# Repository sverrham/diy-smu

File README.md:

# diy-smu
DIY Source Measurement Unit, four quadrant powersupply and ?.? digit volt/current meter.

This is based on http://www.djerickson.com/diy_smu/index.html but with some changes.

- I plan to use the raspberry pi for control, maybe design a front pannel solution using the compute module.

- I want to miniturize it a bit, change 0805 to 0603 as that is also quite easy to solder by hand.

- I do not have to much experience with the analog part but will let this be project to learn from.

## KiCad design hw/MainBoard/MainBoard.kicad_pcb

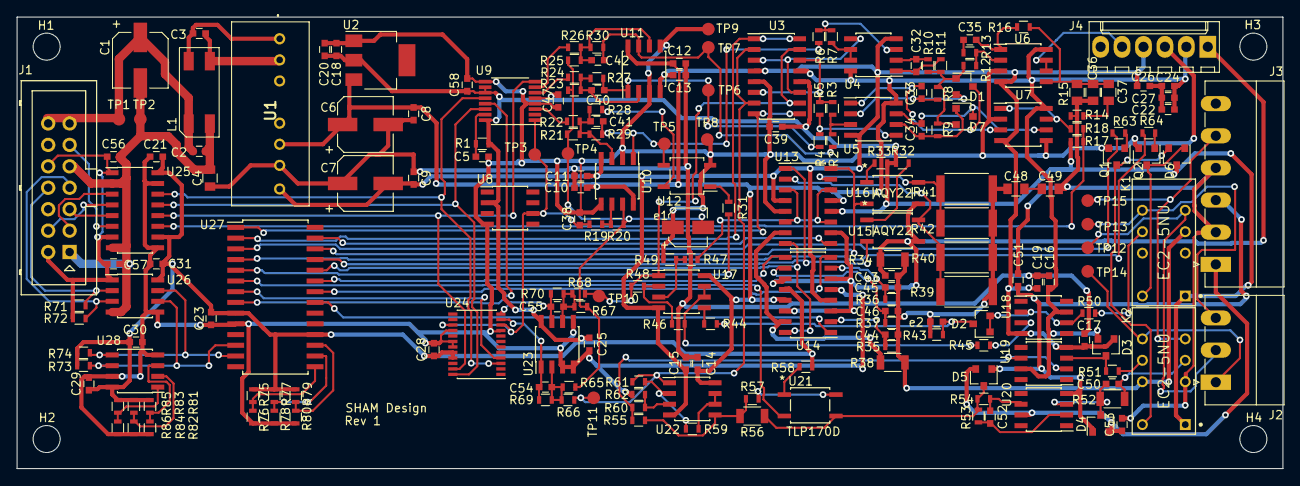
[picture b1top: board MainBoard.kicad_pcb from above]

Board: 2 copper layers, 150.0 x 53.5 mm, 209 parts (0 on the bottom side), 130 nets.

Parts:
C1, C6, C7: 47uf 25V; CP_Elec_6.3x7.7
C2, C3, C8, C9, C18, C20, C57: 4.7u 25V; C_0603
C4: .01u 500V; C_0805
C5, C10, C11, C12, C13, C14, C15, C16, C17, C19, C21, C22, C23, C24, C25, C26, C27, C28, C29, C30, C31, C38, C39, C47, C51, C53, C56, C58: .1u; C_0603
C32, C33, C34: 15p; C_0603
C35, C40, C41, C42, C54, C55: 1000p; C_0603
C36: 22p 500V DNI; C_0805
C37: 150p 500V; C_0805
C43: 100p; C_0603
C44, C45, C46: 270p; C_0603
C48, C49: 270p HIV COG 500V; C_0805
C50: 22p 100V; C_0603
C52: 150p; C_0603
D1: BAV99LT1; SOT-23
D2, D3, D4, D5: BAV199; SOT-23
D6: BAV170; SOT-23
D7: BAV199LT1; SOT-23
H1, H2, H3, H4: MountingHole; MountingHole_3.2mm_M3
J1: Conn_01x14; Multicomp_MC9A12-1434_2x07x2.54mm_Straight
J2: Conn_01x03_Female; PhoenixContact_MC-G_03x3.81mm_Angled
J3: Conn_01x06_Female; PhoenixContact_MC-G_06x3.81mm_Angled
J4: Conn_01x06_Female; Molex_KK-6410-06_06x2.54mm_Straight
K1, K2: EC2-5NU; Kemet-EC2-5NU-0
L1: DR331-105BE; dr331
Q1, Q2: MMBT3904; SOT-23
R1: 100K; R_0603
R2, R3, R4, R5, R6, R7, R19, R20, R21, R22, R23, R24, R25, R26, R55, R59, R60, R61, R62, R65, R67, R69, R70: 10K .1%; R_0603
R8, R9: 20K; R_0603
R10: 20K .1%; R_0603
R11, R17, R51, R54: 4.99K; R_0603
R12, R13, R16, R43, R44, R53, R63, R64: 10K; R_0603
R14, R45: 1K; R_0603
R15: 200K 1206; C_0805
R18: 15K; R_0603
R27, R30, R66, R68: 21.5K .1%; R_0603
R28: 2K .1%; R_0603
R29: 20.5K .1%; R_0603
R31, R32, R33, R50, R58: 2K; R_0603
R34: 5M 25ppm 1206; R_1206
R35: 560K .1%; R_0603
R36: 49.9K .1%; R_0603
R37: 4.99K .1%; R_0603
R38: 499 .25W; R_1206
R39, R40: 100 1W; R_2512
R41, R42: 2 1W; R_2512
R46, R47, R48, R49: 100K .1%; R_0603
R52: 10K 1206; R_1206
R56: 300K .1% 1206; R_1206
R57: 22.1K .1%; R_0603
R71, R72, R73, R74: 1.5K; R_0603
R75, R76, R77, R78, R79, R80, R81, R82, R83, R84, R85, R86: 0; R_0603
TP1: TP+12; Measurement_Point_Round-SMD-Pad_Small
TP2: TPIGND; Measurement_Point_Round-SMD-Pad_Small
TP3: TPR+; Measurement_Point_Round-SMD-Pad_Small
TP4: TPR-; Measurement_Point_Round-SMD-Pad_Small
TP5: TPF; Measurement_Point_Round-SMD-Pad_Small
TP6: TPC-; Measurement_Point_Round-SMD-Pad_Small
TP7: TPC+; Measurement_Point_Round-SMD-Pad_Small
TP8: TPG; Measurement_Point_Round-SMD-Pad_Small
TP9: TPG1; Measurement_Point_Round-SMD-Pad_Small
TP10: TPIM; Measurement_Point_Round-SMD-Pad_Small
TP11: TPVM; Measurement_Point_Round-SMD-Pad_Small
TP12: TP+Out; Measurement_Point_Round-SMD-Pad_Small
TP13: TP+Gua; Measurement_Point_Round-SMD-Pad_Small
TP14: TP+Sen; Measurement_Point_Round-SMD-Pad_Small
TP15: TP-Sen; Measurement_Point_Round-SMD-Pad_Small
U1: DPBW03F; DPBW03F15
U2: LT1117-5.0; SOT-223
U3, U13, U14: DG444; SOIC-16_3.9x9.9mm_Pitch1.27mm
U4, U5, U6, U10, U17, U22: OPA2140; SOIC-8_3.9x4.9mm_Pitch1.27mm
U7: LM393; SOIC-8_3.9x4.9mm_Pitch1.27mm
U8: ADR431ARZ; SOIC-8_3.9x4.9mm_Pitch1.27mm
U9: AD5686RBRUZ; TSSOP-16_4.4x5mm_Pitch0.65mm
U11: TL072; SOIC-8_3.9x4.9mm_Pitch1.27mm
U12: CPC1018N; SOP-4_3.8x4.1mm_Pitch2.54mm
U15, U16: AQY22; TLP170DF
U18: TL071; SOIC-8_3.9x4.9mm_Pitch1.27mm
U19, U20: OPA140; SOIC-8_3.9x4.9mm_Pitch1.27mm
U21: TLP170D; TLP170DF
U23: TLC227x; SOIC-8_3.9x4.9mm_Pitch1.27mm
U24: AD7190BRUZ; TSSOP-24_4.4x7.8mm_Pitch0.65mm
U25: Si8642BB-B-IS1; SOIC-16_3.9x9.9mm_Pitch1.27mm
U26: ISO1541; SOIC-8_3.9x4.9mm_Pitch1.27mm
U27: MCP23017_SO; SOIC-28W_7.5x17.9mm_Pitch1.27mm
U28: 24LC01; SOIC-8_3.9x4.9mm_Pitch1.27mm
e1: 4.7uf 25V; CP_Elec_4x5.3
e2: 22p 100V; C_0603

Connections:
/1A: U13.16, U16.2, U27.26
/1mA: U14.9, U27.23
/10mA: U13.8, U14.16, U27.24
/10uA: U14.1, U27.21
/100mA: U13.1, U15.2, U27.25
/100uA: U14.8, U27.22
/+2.5VREF: C38.1, R19.2, TP3.1, U8.6, U9.1, U24.10, U24.15
/+5V: C18.1, C20.1, C21.1, C23.1, C25.1, C28.1, C29.1, C30.1, C31.1, C39.1, C47.1, C58.1, D6.3, K1.1, K2.1, R1.2, R17.2, R32.1, R33.1, R58.1, R73.1, R74.1, R75.1, R77.1, R79.1, R81.1, R83.1, R85.1, U2.2, U3.12, U8.2, U9.5, U9.10, U9.11, U9.16, U13.12, U14.12, U23.8, U24.20, U24.21, U25.10, U25.16, U26.8, U27.9, U27.18, U28.8
/+5VIN: C56.1, C57.1, J1.2, J1.10, R71.1, R72.1, U25.1, U25.7, U26.1
/+12VIN: C1.1, C2.1, J1.13, J1.14, L1.1, TP1.1
/+15V: C6.1, C8.1, C10.1, C12.1, C14.1, C16.1, C22.1, C24.1, C27.1, D3.2, J4.2, U1.6, U2.3, U3.13, U4.8, U5.8, U6.8, U7.8, U10.8, U11.8, U13.13, U14.13, U17.8, U18.7, U19.7, U22.8
/-2.5VREF: R20.1, R21.2, R23.2, R25.2, R65.2, R67.2, TP4.1, U10.7, e1.2
/-15V: C7.2, C9.2, C11.2, C13.2, C15.2, C17.2, C19.2, C26.2, D3.1, J4.4, U1.8, U3.4, U4.4, U5.4, U6.4, U7.4, U10.4, U11.4, U13.4, U14.4, U17.4, U18.4, U19.4, U22.4
/ADC/IM: R48.1, R68.2, TP10.1, U3.10, U3.15, U17.1
/ADC/IMADC: C55.2, R70.1, U23.7, U24.12
/ADC/VM: R61.1, R66.2, TP11.1, U3.2, U3.7, U22.1
/ADC/VMADC: C54.2, R69.1, U23.1, U24.11
/CLAMP: J1.11, U25.6
/CS_ADC: U24.4, U27.7
/CS_DAC: U9.13, U27.8
/FDACLO: R31.1, U27.5
/ICLAMP: R17.1, R18.2, U25.11
/IIC_SCL: J1.7, R72.2, U26.3
/IIC_SDA: J1.8, R71.2, U26.2
/IMISO: U9.8, U24.23, U25.12
/IMODE: U3.8, U3.9, U27.1
/IMOSI: U9.14, U24.24, U25.13
/ISCK: U9.12, U24.3, U25.14
/Isolation and Controll/ISCL: R73.2, U26.6, U27.12, U28.6
/Isolation and Controll/ISDA: R74.2, U26.7, U27.13, U28.5
/LT10mA: U13.9, U27.27
/MISO: J1.5, U25.5
/MOSI: J1.4, U25.4
/OCOM: C36.1, C49.2, C51.2, C53.2, J3.2, J3.4, K2.3, R14.2, R15.2
/ON: R64.2, U27.4
/REMOTE: R63.2, U27.3
/SCK: J1.3, U25.3
/VMODE: U3.1, U3.16, U27.2
/VRANGEL: U21.2, U27.6
/crossover/AMPIN: J4.5, U6.6, U6.7
/crossover/CL+: C42.1, R2.2, R30.1, TP7.1, U11.7
/crossover/CL-: C40.2, R4.2, R27.1, TP6.1, U11.1
/crossover/CLM: R3.2, R5.2, U3.6, U3.14
/crossover/FDACN: C41.1, R6.2, R29.1, TP5.1, U10.1, U12.3
/crossover/FM: R7.2, U4.6, U4.7
/crossover/INT: C35.2, R16.2, U6.1
/current measure/+Guard: K1.9, R50.1
/current measure/+OUT_INT: C43.1, C44.1, C45.1, C46.1, C48.1, K1.4, K2.10, R34.1, R35.1, R36.1, R37.1, R38.1, R39.1, R40.1, R41.1, R42.1, R43.2, e2.2
/current measure/AMPGND: C43.2, J4.1, R34.2, U13.10, U14.3, U14.6, U14.11, U14.14, U15.3, U16.3
/current measure/INT_GUARD: D2.1, D2.2, R50.2, U18.2, U18.6
/dac/DAC_CL+: R26.2, U9.7
/dac/DAC_CL-: R24.2, U9.6
/dac/DAC_F: R22.2, U9.3
/frontend/+15VOUT: C53.1, D4.2, D5.2, J3.1, U20.7
/frontend/+GOUT: J2.3, K1.8, TP13.1
/frontend/+OUT: J2.2, K1.5, TP12.1
/frontend/+SEN: J2.1, K2.8, TP14.1
/frontend/+SEN_INT: K2.9, R51.2
/frontend/-15VOUT: C51.1, D4.1, D5.1, J3.3, U20.4
/frontend/-SEN: J3.5, K2.5, TP15.1
/frontend/-SEN_INT: C50.2, K2.4, R52.2
/frontend/ON_RLY: D6.1, K1.12, Q2.3
/frontend/REM_RLY: D6.2, K2.12, Q1.3
/reset: C5.1, R1.1, U9.15
GND1: C5.2, C18.2, C20.2, C21.2, C23.2, C25.2, C28.2, C29.2, C30.2, C31.2, C38.2, C39.2, C47.2, C58.2, J4.3, Q1.2, Q2.2, R49.1, R62.1, R76.2, R78.2, R80.2, R82.2, R84.2, R86.2, TP8.1, TP9.1, U2.1, U3.5, U6.3, U7.2, U7.5, U8.4, U9.4, U9.9, U10.2, U10.5, U11.3, U11.5, U12.2, U13.5, U14.5, U23.3, U23.4, U23.5, U24.9, U24.16, U24.18, U24.19, U25.9, U25.15, U26.5, U27.10, U28.4, U28.7, e1.1
GNDREF: C1.2, C2.2, C4.2, C56.2, C57.2, J1.1, J1.9, L1.2, TP2.1, U25.2, U25.8, U26.4
unnamed: C3.1, L1.4, U1.1
unnamed: C3.2, L1.3, U1.2
unnamed: C4.1, C6.2, C7.1, C8.2, C9.1, C10.2, C11.1, C12.2, C13.1, C14.2, C15.1, C16.2, C17.1, C19.1, U1.7
unnamed: C22.2, C24.2, C26.1, C27.2
unnamed: C32.1, R10.2, U4.2
unnamed: C32.2, R11.2, U4.1
unnamed: C33.1, D1.3, U5.1, U7.3
unnamed: C33.2, D1.2, R8.2, U5.2
unnamed: C34.1, D7.3, U5.7, U7.6
unnamed: C34.2, D7.1, R9.2, U5.6
unnamed: C35.1, R13.1
unnamed: C36.2, C37.2, R15.1, R16.1, U6.5
unnamed: C37.1, R14.1
unnamed: C40.1, R23.1, R24.1, R27.2, U11.2
unnamed: C41.2, R21.1, R22.1, R28.2, R29.2, U10.3
unnamed: C42.2, R25.1, R26.1, R30.2, U11.6
unnamed: C44.2, R35.2, U14.2
unnamed: C45.2, R36.2, U14.7
unnamed: C46.2, R37.2, U14.10
unnamed: C48.2, C49.1
unnamed: C50.1, D4.3, R52.1, U20.3
unnamed: C52.1, R54.2, U20.6
unnamed: C52.2, R53.2, U20.2
unnamed: C54.1, R65.1, R66.1, R69.2, U23.2
unnamed: C55.1, R67.1, R68.1, R70.2, U23.6
unnamed: D1.1, D7.2, R8.1, R9.1, R10.1, R11.1, R12.2
unnamed: D2.3, R43.1, R44.2, e2.1
unnamed: D3.3, R51.1, U19.3
unnamed: D5.3, R53.1, R54.1, R56.2, U21.3
unnamed: Q1.1, R63.1
unnamed: Q2.1, R64.1
unnamed: R2.1, R3.1, U5.3
unnamed: R4.1, R5.1, U5.5
unnamed: R6.1, R7.1, U4.3
unnamed: R12.1, R13.2, U6.2
unnamed: R18.1, U7.1, U7.7
unnamed: R19.1, R20.2, U10.6
unnamed: R28.1, U12.4
unnamed: R31.2, U12.1
unnamed: R32.2, U15.1
unnamed: R33.2, U16.1
unnamed: R38.2, U13.7, U14.15
unnamed: R39.2, R40.2, U13.2, U15.4
unnamed: R41.2, R42.2, U13.15, U16.4
unnamed: R44.1, U17.5
unnamed: R45.1, U18.3
unnamed: R45.2, R46.2, U17.6, U17.7
unnamed: R46.1, R48.2, U17.2
unnamed: R47.1, R49.2, U17.3
unnamed: R47.2, U13.3, U13.6, U13.11, U13.14
unnamed: R55.1, R60.2, U19.2, U19.6
unnamed: R55.2, R56.1, R57.1, U22.5
unnamed: R57.2, U21.4
unnamed: R58.2, U21.1
unnamed: R59.1, R61.2, U22.2
unnamed: R59.2, U22.6, U22.7
unnamed: R60.1, R62.2, U22.3
unnamed: R75.2, R76.1, U27.15
unnamed: R77.2, R78.1, U27.16
unnamed: R79.2, R80.1, U27.17
unnamed: R81.2, R82.1, U28.3
unnamed: R83.2, R84.1, U28.2
unnamed: R85.2, R86.1, U28.1
unnamed: U3.3, U3.11, U4.5

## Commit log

2021-03-08 Initial commit with main board
2021-03-08 Updated description
2021-03-08 add ignore files
2021-03-08 Add footprints uesd
2021-03-08 Added pdf
2021-03-09 Fix issues with footprints, missing solder mask
2021-03-09 Update schema, fix wrong package for BAV99 D1, add mounting holes to schema.
2021-03-09 Updated layout with updated schema

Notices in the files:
parts and their libraries:
Copyright 2016 Accelerated Designs. All rights reserved.
